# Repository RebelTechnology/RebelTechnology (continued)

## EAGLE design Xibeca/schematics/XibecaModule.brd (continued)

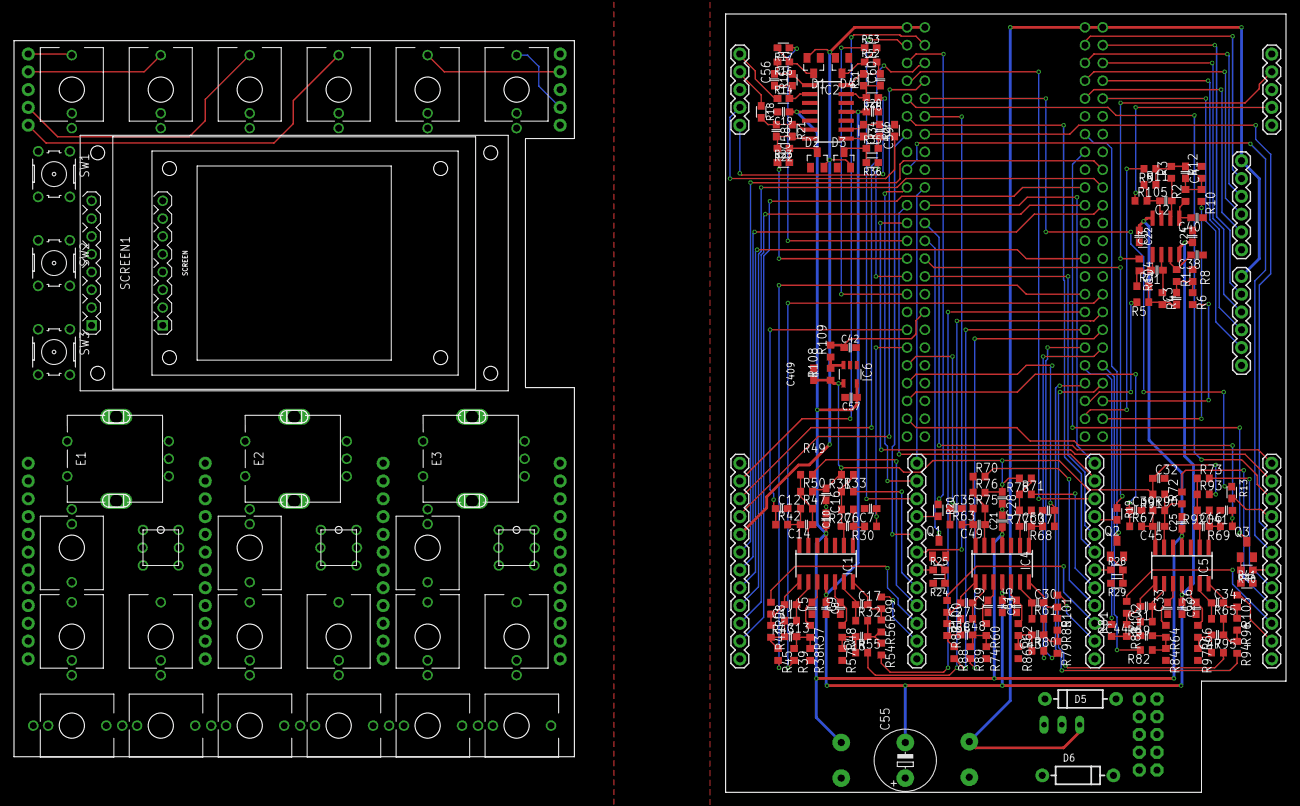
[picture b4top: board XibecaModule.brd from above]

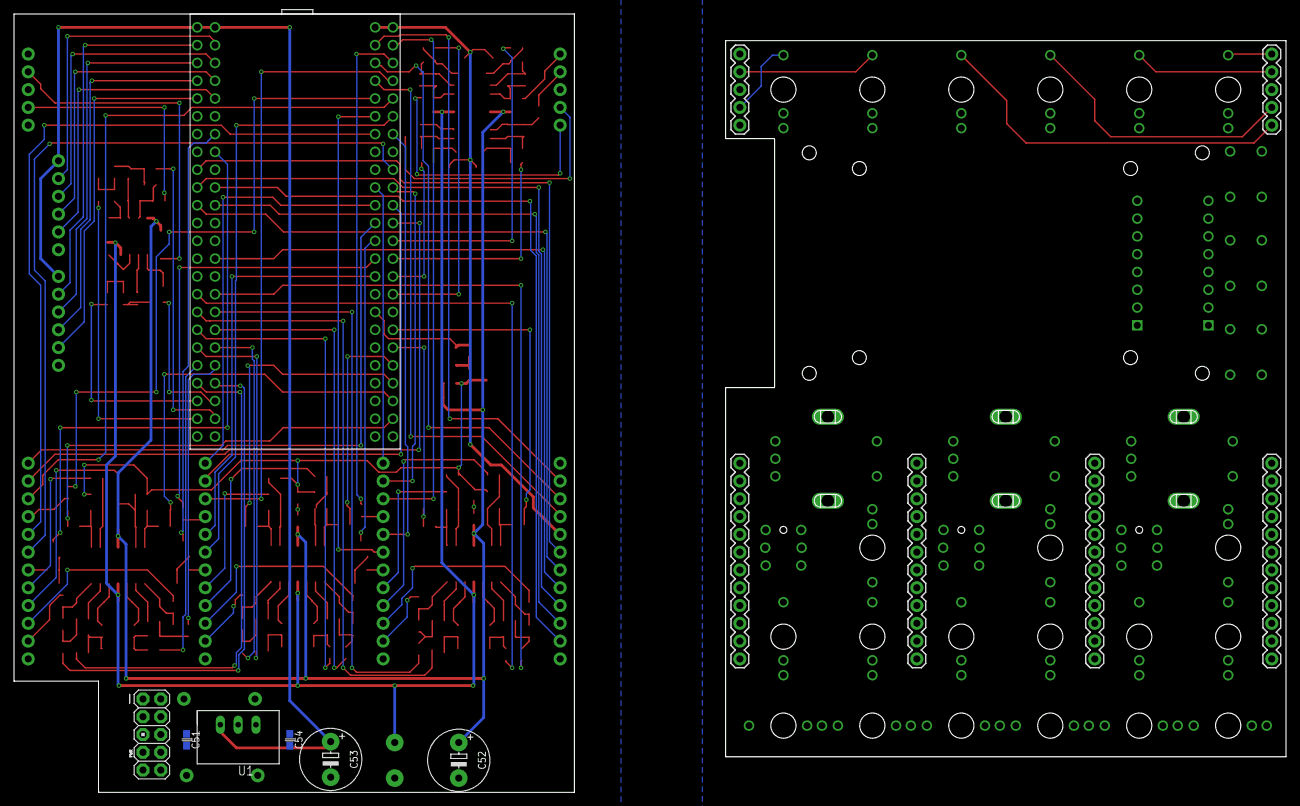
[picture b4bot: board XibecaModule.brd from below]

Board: 2 copper layers, 80.0 x 111.1 mm, 232 parts (13 on the bottom side), 183 nets.

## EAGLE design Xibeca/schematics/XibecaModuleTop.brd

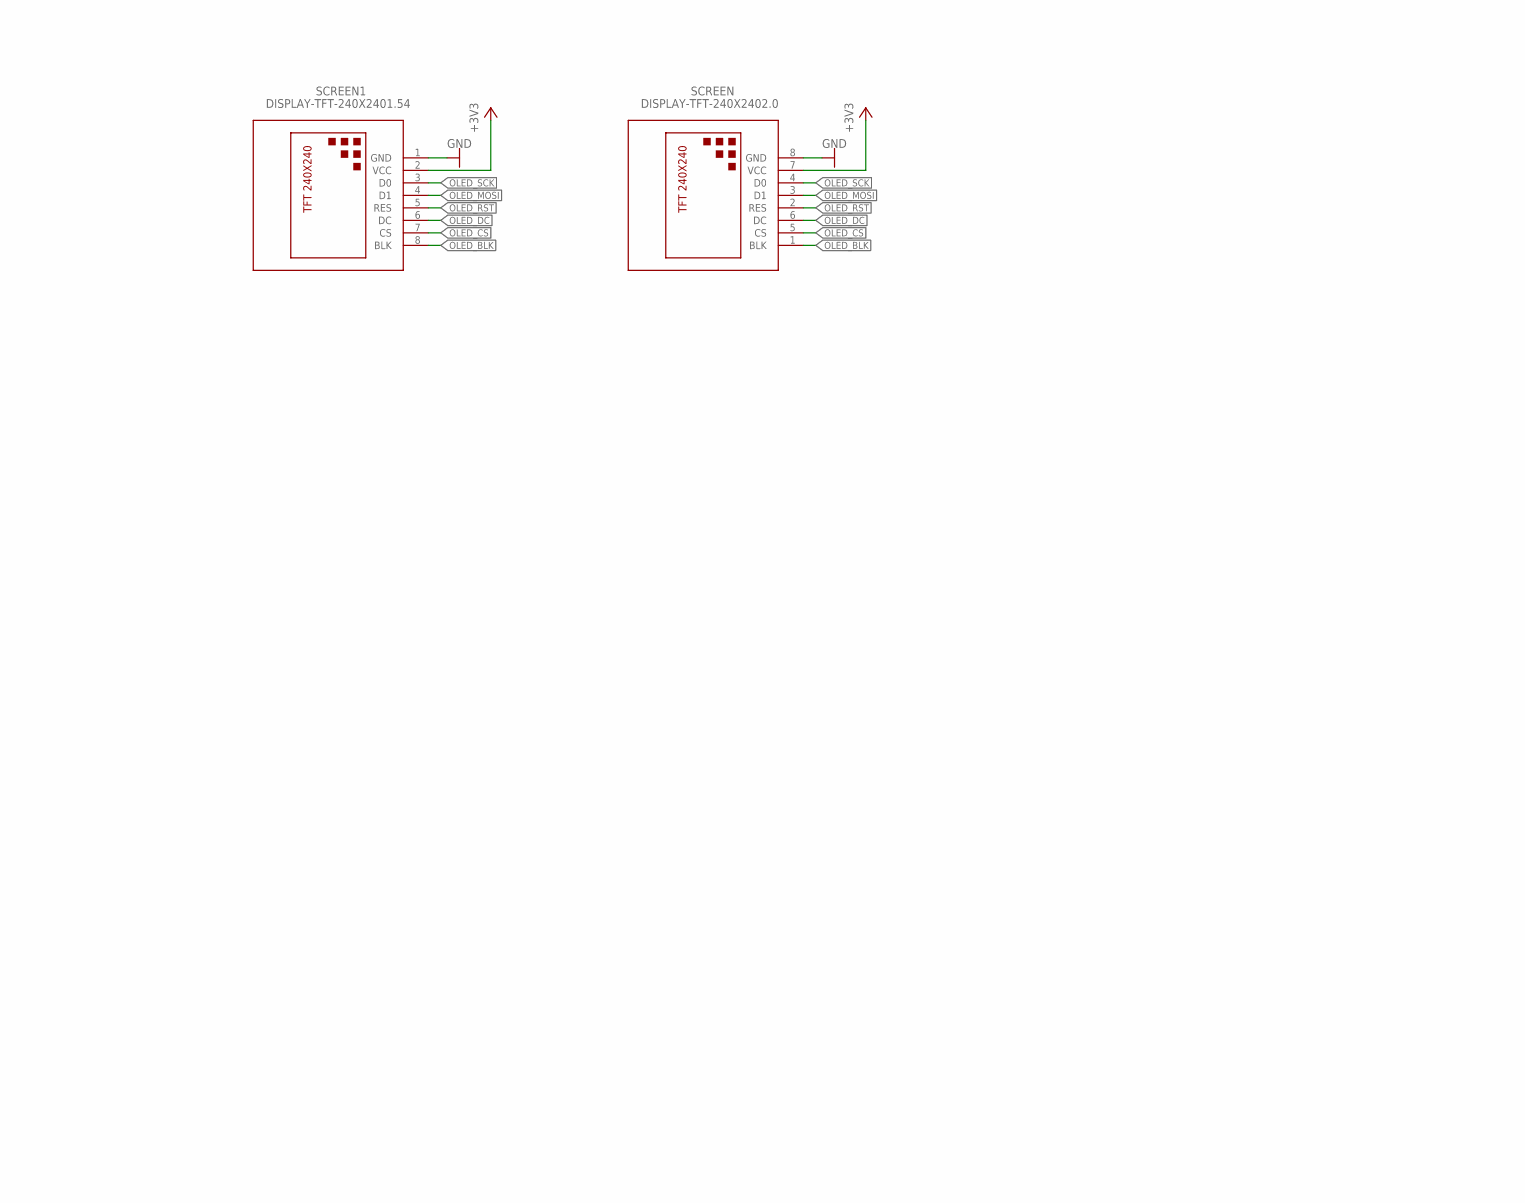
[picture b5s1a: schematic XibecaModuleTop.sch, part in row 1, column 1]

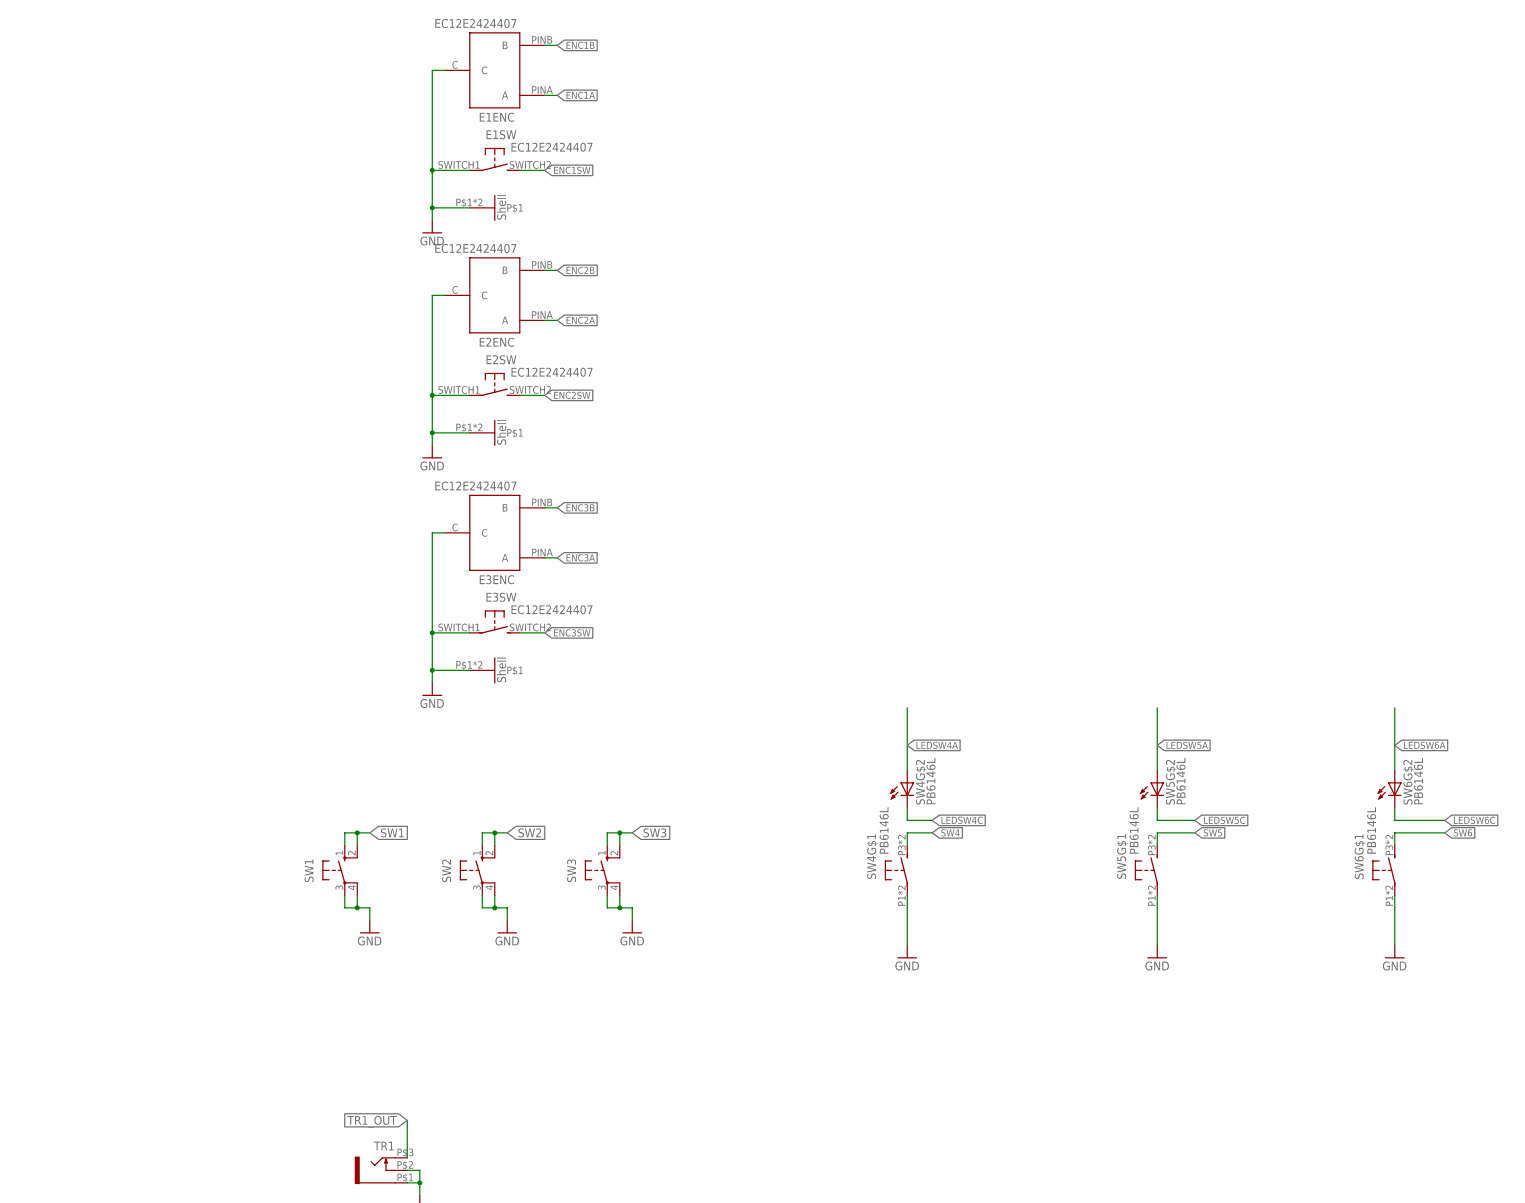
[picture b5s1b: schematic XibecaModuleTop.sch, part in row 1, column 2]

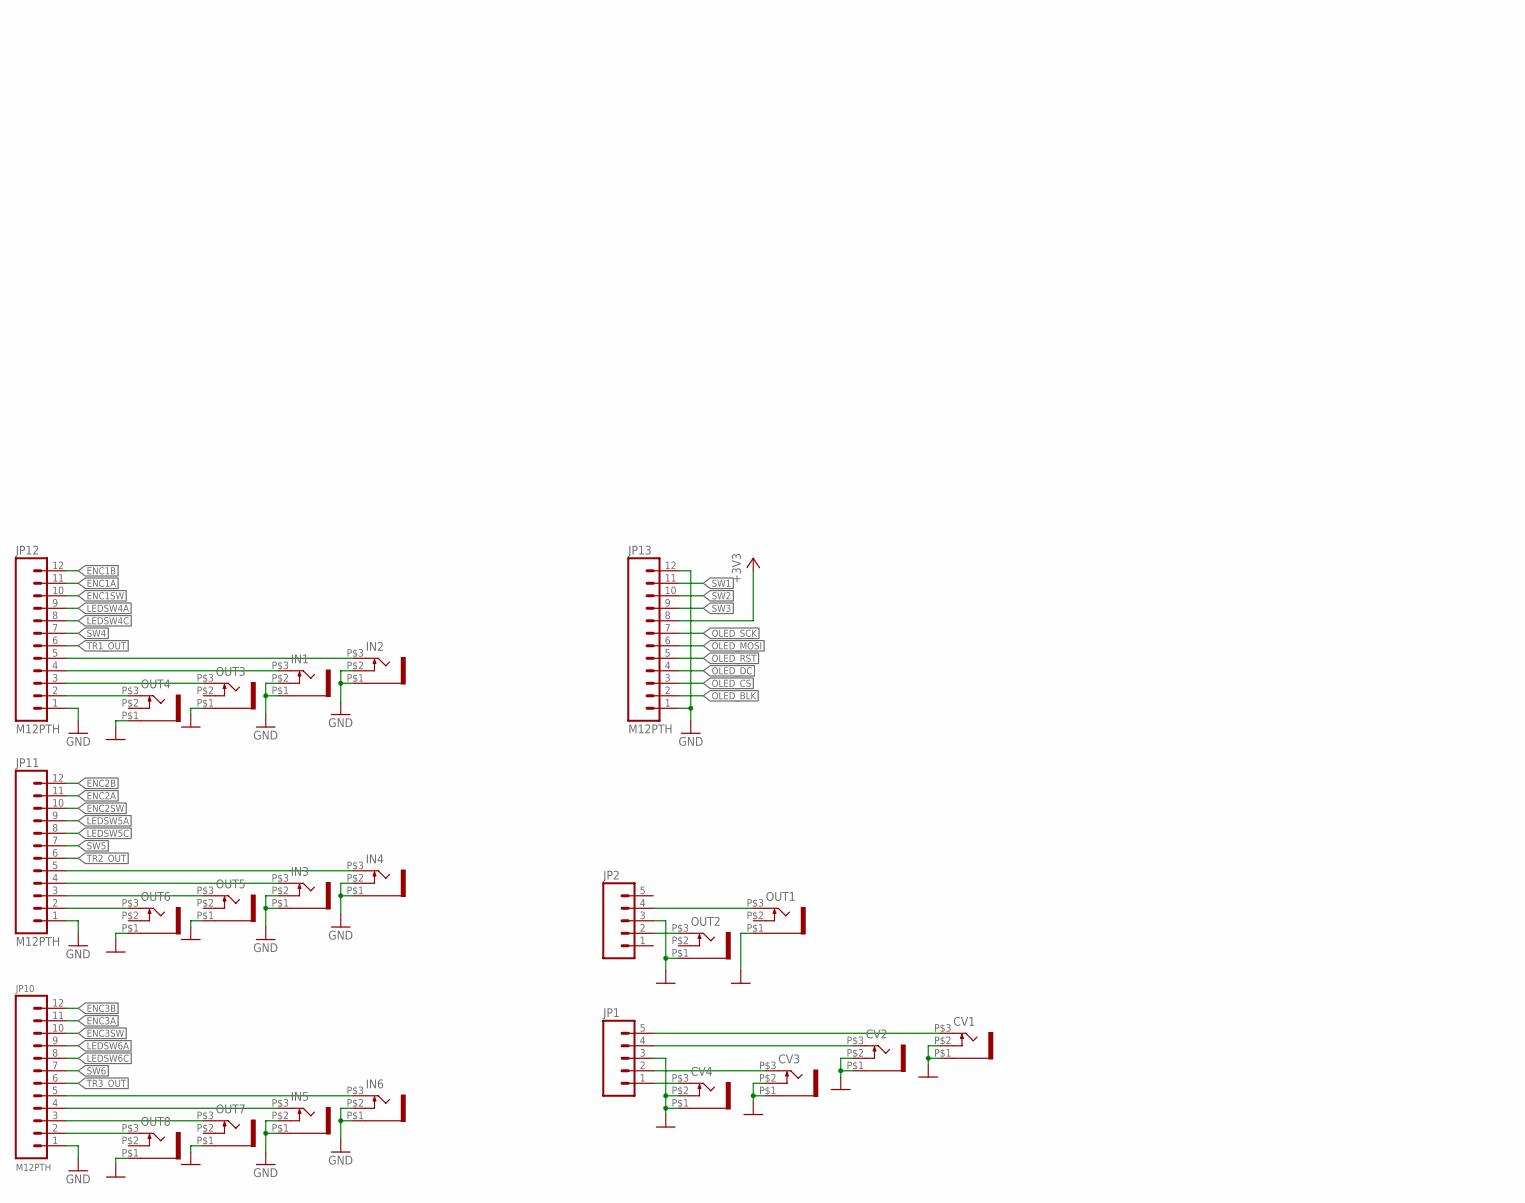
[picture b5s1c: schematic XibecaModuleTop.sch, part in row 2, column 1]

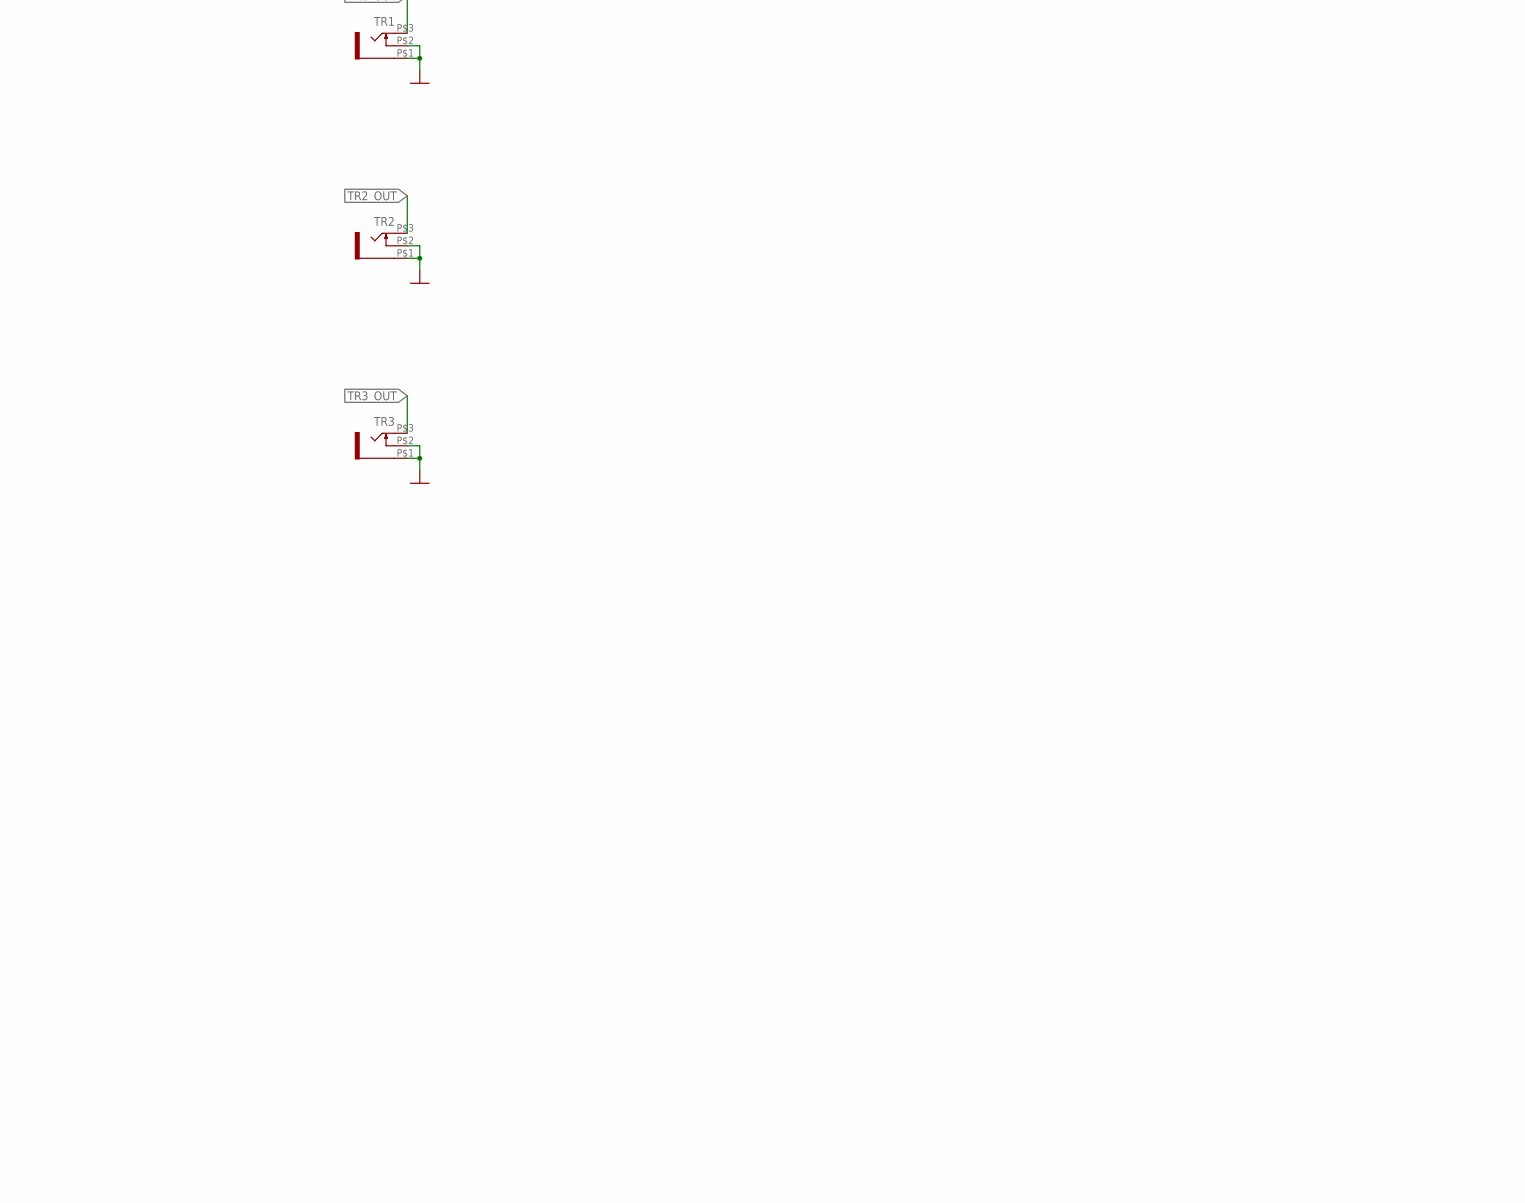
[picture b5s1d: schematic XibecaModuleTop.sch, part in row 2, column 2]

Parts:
CV1, CV2, CV3, CV4: THONKICONN
E1, E2, E3: EC12E2424407
IN1, IN2, IN3, IN4, IN5, IN6: THONKICONN
JP1, JP2: M05PTH; 1X05
JP10, JP11, JP12, JP13: M12PTH; 1X12
OUT1, OUT2, OUT3, OUT4, OUT5, OUT6, OUT7, OUT8: THONKICONN
SCREEN: DISPLAY-TFT-240X2402.0; DISPLAY-TFT-240X320-2.0"
SCREEN1: DISPLAY-TFT-240X2401.54; DISPLAY-TFT-240X240-1.54"
SW1, SW2, SW3: 10-XX; B3F-10XX
SW4, SW5, SW6: PB6146L
TR1, TR2, TR3: THONKICONN

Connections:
+3V3: JP13.8, SCREEN.7 (VCC), SCREEN1.2 (VCC)
ENC1A: E1.PINA (A), JP12.11
ENC1B: E1.PINB (B), JP12.12
ENC1SW: E1.SWITCH2 (S), JP12.10
ENC2A: E2.PINA (A), JP11.11
ENC2B: E2.PINB (B), JP11.12
ENC2SW: E2.SWITCH2 (S), JP11.10
ENC3A: E3.PINA (A), JP10.11
ENC3B: E3.PINB (B), JP10.12
ENC3SW: E3.SWITCH2 (S), JP10.10
GND: CV1.P$1 (5), CV1.P$2 (4), CV2.P$1 (5), CV2.P$2 (4), CV3.P$1 (5), CV3.P$2 (4), CV4.P$1 (5), CV4.P$2 (4), E1.C, E1.P$1, E1.P$2, E1.SWITCH1, E2.C, E2.P$1, E2.P$2, E2.SWITCH1, E3.C, E3.P$1, E3.P$2, E3.SWITCH1, IN1.P$1 (5), IN1.P$2 (4), IN2.P$1 (5), IN2.P$2 (4), IN3.P$1 (5), IN3.P$2 (4), IN4.P$1 (5), IN4.P$2 (4), IN5.P$1 (5), IN5.P$2 (4), IN6.P$1 (5), IN6.P$2 (4), JP1.3, JP2.3, JP10.1, JP11.1, JP12.1, JP13.1, JP13.12, OUT1.P$1 (5), OUT2.P$1 (5), OUT3.P$1 (5), OUT4.P$1 (5), OUT5.P$1 (5), OUT6.P$1 (5), OUT7.P$1 (5), OUT8.P$1 (5), SCREEN.8 (GND), SCREEN1.1 (GND), SW1.3, SW1.4 (P1), SW2.3, SW2.4 (P1), SW3.3, SW3.4 (P1), SW4.P1, SW4.P2, SW5.P1, SW5.P2, SW6.P1, SW6.P2, TR1.P$1 (5), TR1.P$2 (4), TR2.P$1 (5), TR2.P$2 (4), TR3.P$1 (5), TR3.P$2 (4)
LEDSW4A: JP12.9, SW4.PL1 (A)
LEDSW4C: JP12.8, SW4.PL2 (C)
LEDSW5A: JP11.9, SW5.PL1 (A)
LEDSW5C: JP11.8, SW5.PL2 (C)
LEDSW6A: JP10.9, SW6.PL1 (A)
LEDSW6C: JP10.8, SW6.PL2 (C)
unnamed: IN2.P$3 (3), JP12.5
unnamed: IN1.P$3 (3), JP12.4
unnamed: JP12.3, OUT3.P$3 (3)
unnamed: JP12.2, OUT4.P$3 (3)
unnamed: JP11.2, OUT6.P$3 (3)
unnamed: JP11.3, OUT5.P$3 (3)
unnamed: JP2.4, OUT1.P$3 (3)
unnamed: JP2.2, OUT2.P$3 (3)
unnamed: IN3.P$3 (3), JP11.4
unnamed: IN4.P$3 (3), JP11.5
unnamed: JP10.2, OUT8.P$3 (3)
unnamed: JP10.3, OUT7.P$3 (3)
unnamed: IN5.P$3 (3), JP10.4
unnamed: IN6.P$3 (3), JP10.5
unnamed: CV4.P$3 (3), JP1.1
unnamed: CV1.P$3 (3), JP1.5
unnamed: CV2.P$3 (3), JP1.4
unnamed: CV3.P$3 (3), JP1.2
OLED_BLK: JP13.2, SCREEN.1 (BLK), SCREEN1.8 (BLK)
OLED_CS: JP13.3, SCREEN.5 (CS), SCREEN1.7 (CS)
OLED_DC: JP13.4, SCREEN.6 (DC), SCREEN1.6 (DC)
OLED_MOSI: JP13.6, SCREEN.3 (D1), SCREEN1.4 (D1)
OLED_RST: JP13.5, SCREEN.2 (RES), SCREEN1.5 (RES)
OLED_SCK: JP13.7, SCREEN.4 (D0), SCREEN1.3 (D0)
SW1: JP13.11, SW1.1 (S), SW1.2 (S1)
SW2: JP13.10, SW2.1 (S), SW2.2 (S1)
SW3: JP13.9, SW3.1 (S), SW3.2 (S1)
SW4: JP12.7, SW4.P3 (S), SW4.P4 (S)
SW5: JP11.7, SW5.P3 (S), SW5.P4 (S)
SW6: JP10.7, SW6.P3 (S), SW6.P4 (S)
TR1_OUT: JP12.6, TR1.P$3 (3)
TR2_OUT: JP11.6, TR2.P$3 (3)
TR3_OUT: JP10.6, TR3.P$3 (3)

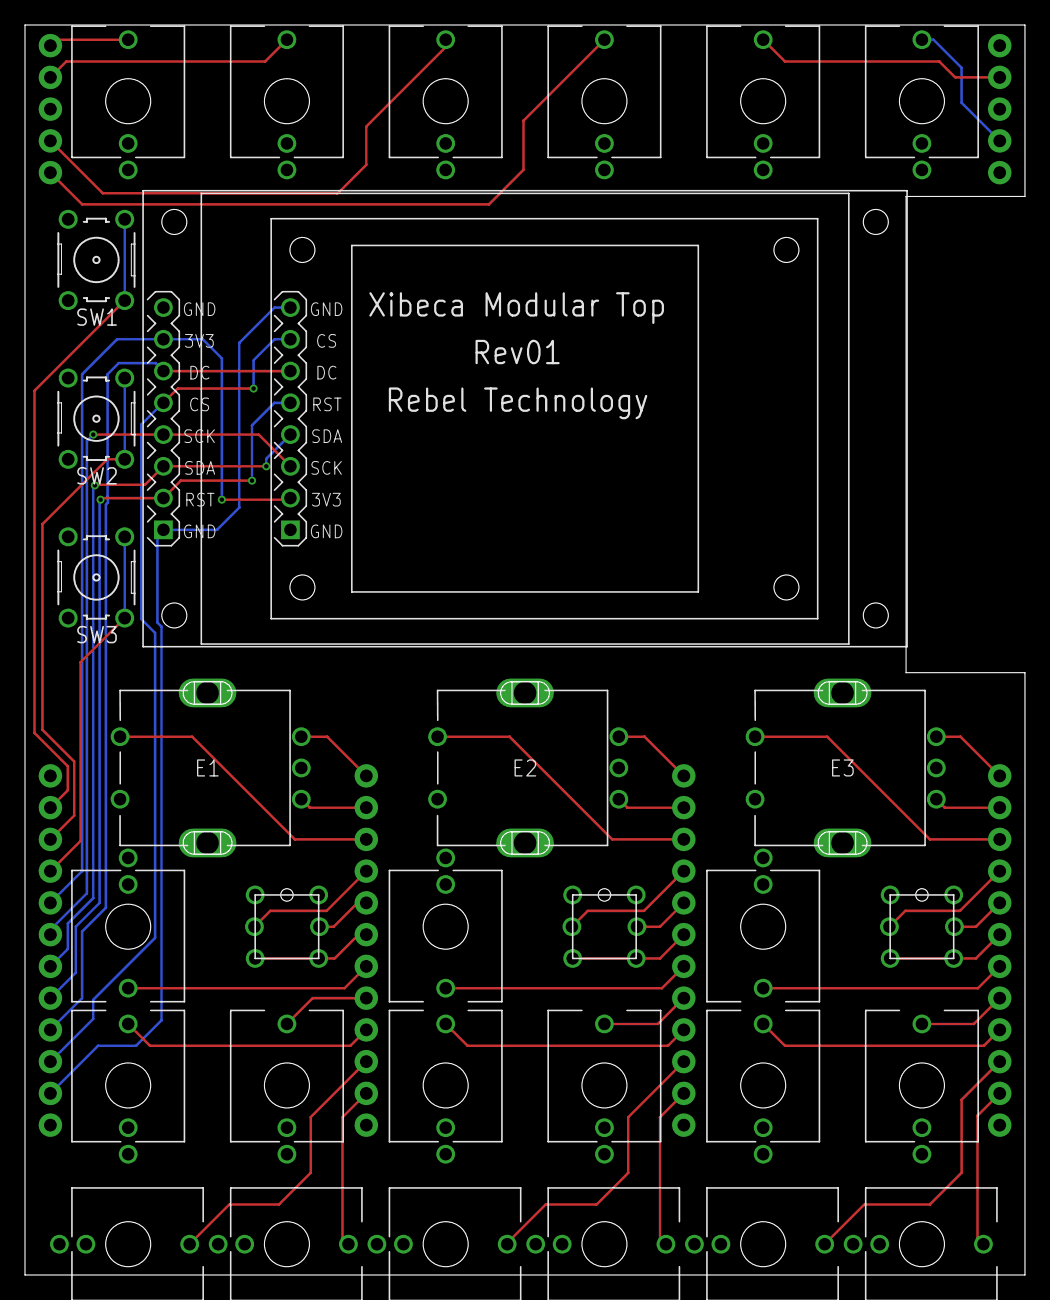
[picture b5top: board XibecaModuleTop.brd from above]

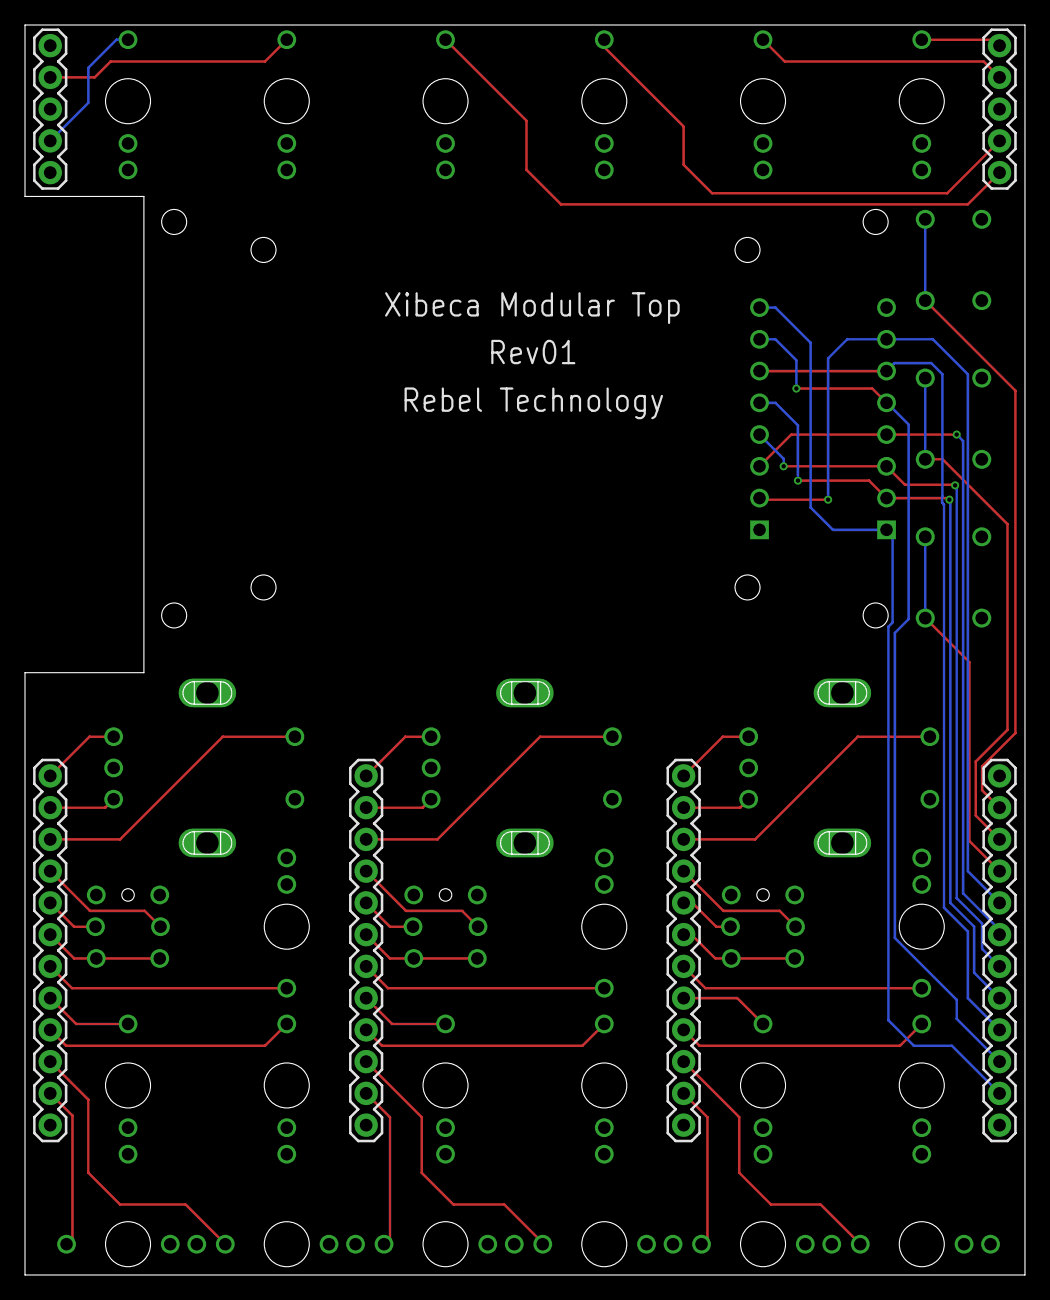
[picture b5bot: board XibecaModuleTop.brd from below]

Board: 2 copper layers, 80.0 x 100.0 mm, 38 parts (6 on the bottom side), 50 nets.

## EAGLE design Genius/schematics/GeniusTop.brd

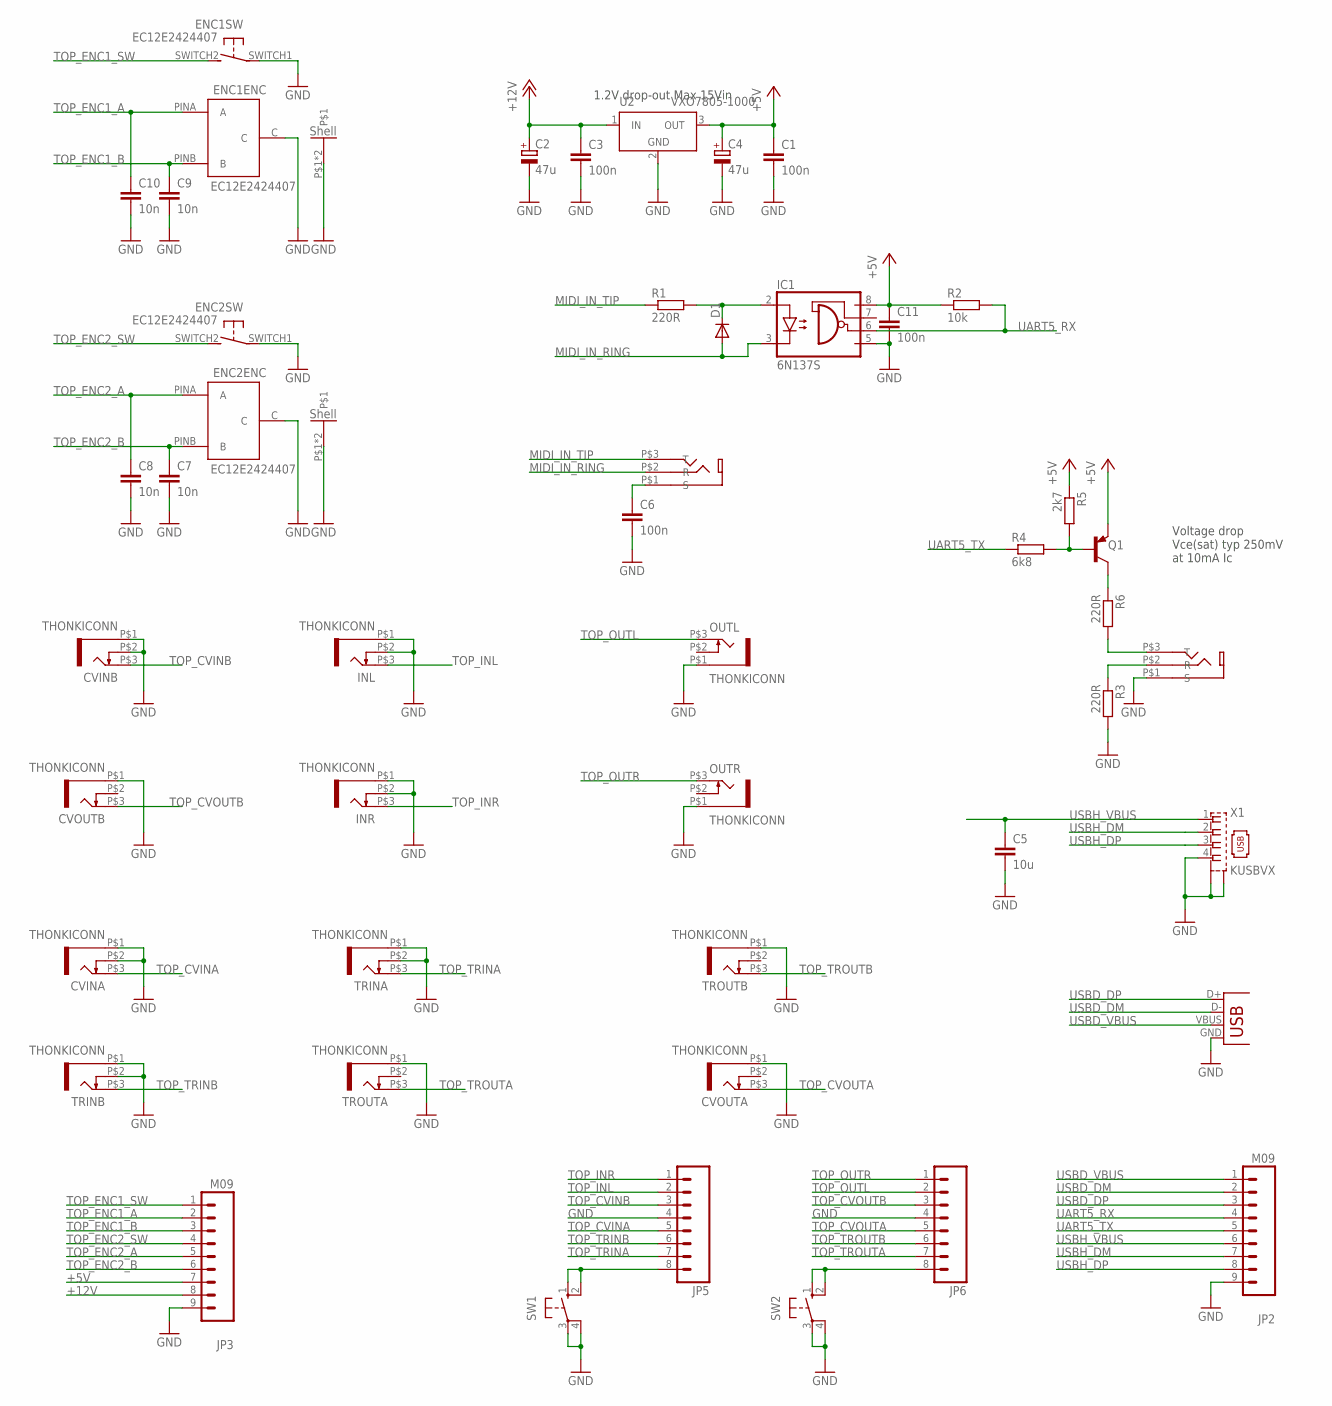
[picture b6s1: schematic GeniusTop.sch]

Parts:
C1, C3, C6, C11: 100n; C0603
C2, C4: 47u; CPOL-5
C5: 10u; C1206
C7, C8, C9, C10: 10n; C0603
CVINA: THONKICONN
CVINB: THONKICONN
CVOUTA: THONKICONN
CVOUTB: THONKICONN
D1: DIODESOD-123; SOD-123
ENC1, ENC2: EC12E2424407
IC1: 6N137S; DIL8-SMD
INL: THONKICONN
INR: THONKICONN
JP2, JP3: M09; 1X09
JP5, JP6: M081X08; 1X08
MIDI_IN: THONKICONN_STEREO
MIDI_OUT: THONKICONN_STEREO
OUTL: THONKICONN
OUTR: THONKICONN
Q1: MMBT3906LT1-PNP-SOT23-BEC; SOT23-BEC
R1, R3, R6: 220R; 0603
R2: 10k; 0603
R4: 6k8; 0603
R5: 2k7; 0603
SW1, SW2: 10-XX; B3F-10XX
TRINA: THONKICONN
TRINB: THONKICONN
TROUTA: THONKICONN
TROUTB: THONKICONN
U2: VXO7805-1000; TSR-1-2450
X1: KUSBVX
X2: USBPTH-VERTICAL; USB-B-PTH-VERTICAL

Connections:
+5V: C1.1, C4.+, C11.1, IC1.8 (VCC), JP3.7, Q1.E, R2.1, R5.1, U2.3 (OUT)
+12V: C2.+, C3.1, JP3.8, U2.1 (IN)
GND: C1.2, C2.-, C3.2, C4.-, C5.2, C6.2, C7.2, C8.2, C9.2, C10.2, C11.2, CVINA.P$1 (5), CVINA.P$2 (4), CVINB.P$1 (5), CVINB.P$2 (4), CVOUTA.P$1 (5), CVOUTB.P$1 (5), ENC1.C, ENC1.P$1, ENC1.P$2, ENC1.SWITCH1, ENC2.C, ENC2.P$1, ENC2.P$2, ENC2.SWITCH1, IC1.5 (GND), INL.P$1 (5), INL.P$2 (4), INR.P$1 (5), INR.P$2 (4), JP2.9, JP3.9, JP5.4, JP6.4, MIDI_OUT.P$1 (S), OUTL.P$1 (5), OUTR.P$1 (5), R3.2, SW1.3, SW1.4 (P1), SW2.3, SW2.4 (P1), TRINA.P$1 (5), TRINA.P$2 (4), TRINB.P$1 (5), TRINB.P$2 (4), TROUTA.P$1 (5), TROUTB.P$1 (5), U2.2 (GND), X1.4, X1.M1 (S1), X1.M2 (S2), X2.GND
MIDI_IN_RING: D1.A, IC1.3 (C), MIDI_IN.P$2 (R)
MIDI_IN_TIP: MIDI_IN.P$3 (T), R1.1
MIDI_OUT_TIP: MIDI_OUT.P$3 (T), R6.2
unnamed: D1.C, IC1.2 (A), R1.2
unnamed: C6.1, MIDI_IN.P$1 (S)
unnamed: JP5.8, SW1.1 (S), SW1.2 (S1)
unnamed: JP6.8, SW2.1 (S), SW2.2 (S1)
unnamed: Q1.B, R4.2, R5.2
unnamed: MIDI_OUT.P$2 (R), R3.1
unnamed: Q1.C, R6.1
TOP_CVINA: CVINA.P$3 (3), JP5.5
TOP_CVINB: CVINB.P$3 (3), JP5.3
TOP_CVOUTA: CVOUTA.P$3 (3), JP6.5
TOP_CVOUTB: CVOUTB.P$3 (3), JP6.3
TOP_ENC1_A: C10.1, ENC1.PINA (A), JP3.2
TOP_ENC1_B: C9.1, ENC1.PINB (B), JP3.3
TOP_ENC1_SW: ENC1.SWITCH2 (S), JP3.1
TOP_ENC2_A: C8.1, ENC2.PINA (A), JP3.5
TOP_ENC2_B: C7.1, ENC2.PINB (B), JP3.6
TOP_ENC2_SW: ENC2.SWITCH2 (S), JP3.4
TOP_INL: INL.P$3 (3), JP5.2
TOP_INR: INR.P$3 (3), JP5.1
TOP_OUTL: JP6.2, OUTL.P$3 (3)
TOP_OUTR: JP6.1, OUTR.P$3 (3)
TOP_TRINA: JP5.7, TRINA.P$3 (3)
TOP_TRINB: JP5.6, TRINB.P$3 (3)
TOP_TROUTA: JP6.7, TROUTA.P$3 (3)
TOP_TROUTB: JP6.6, TROUTB.P$3 (3)
UART5_RX: IC1.6 (VO), JP2.4, R2.2
UART5_TX: JP2.5, R4.1
USBD_DM: JP2.2, X2.D-
USBD_DP: JP2.3, X2.D+
USBD_VBUS: JP2.1, X2.VBUS
USBH_DM: JP2.7, X1.2
USBH_DP: JP2.8, X1.3
USBH_VBUS: C5.1, JP2.6, X1.1

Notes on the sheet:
1.2V drop-out Max 15Vin
Voltage drop Vce(sat) typ 250mV at 10mA Ic

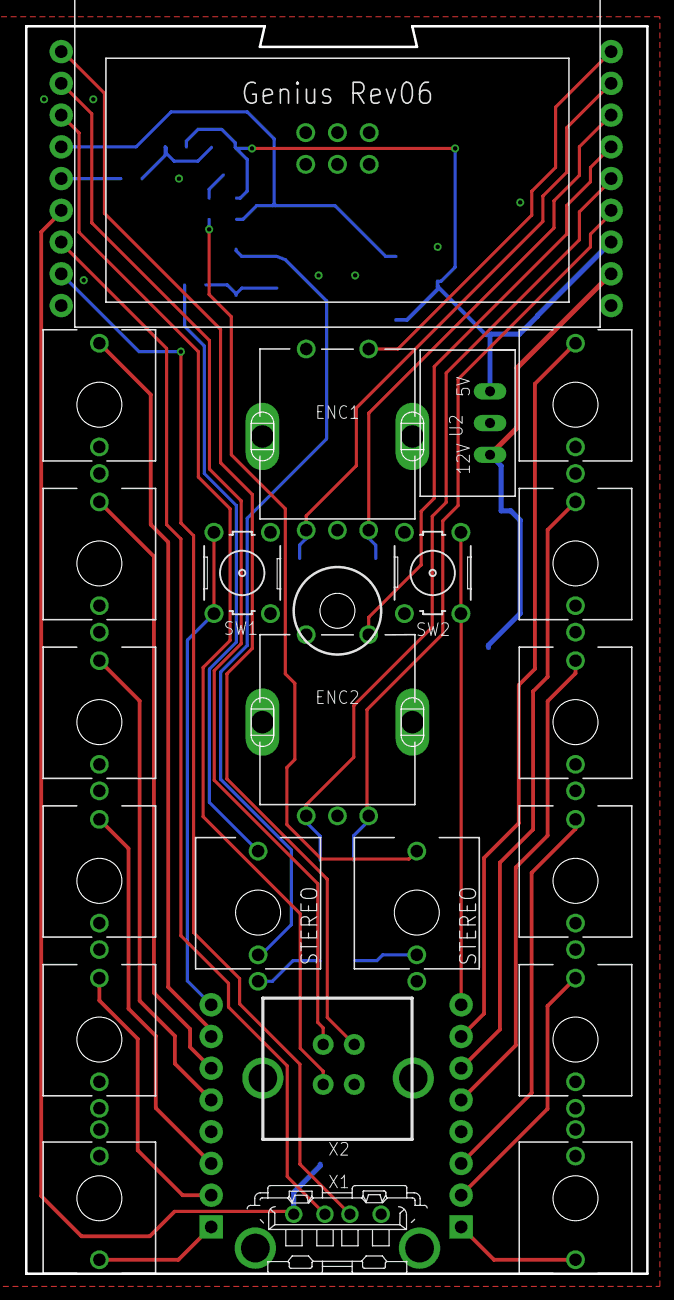
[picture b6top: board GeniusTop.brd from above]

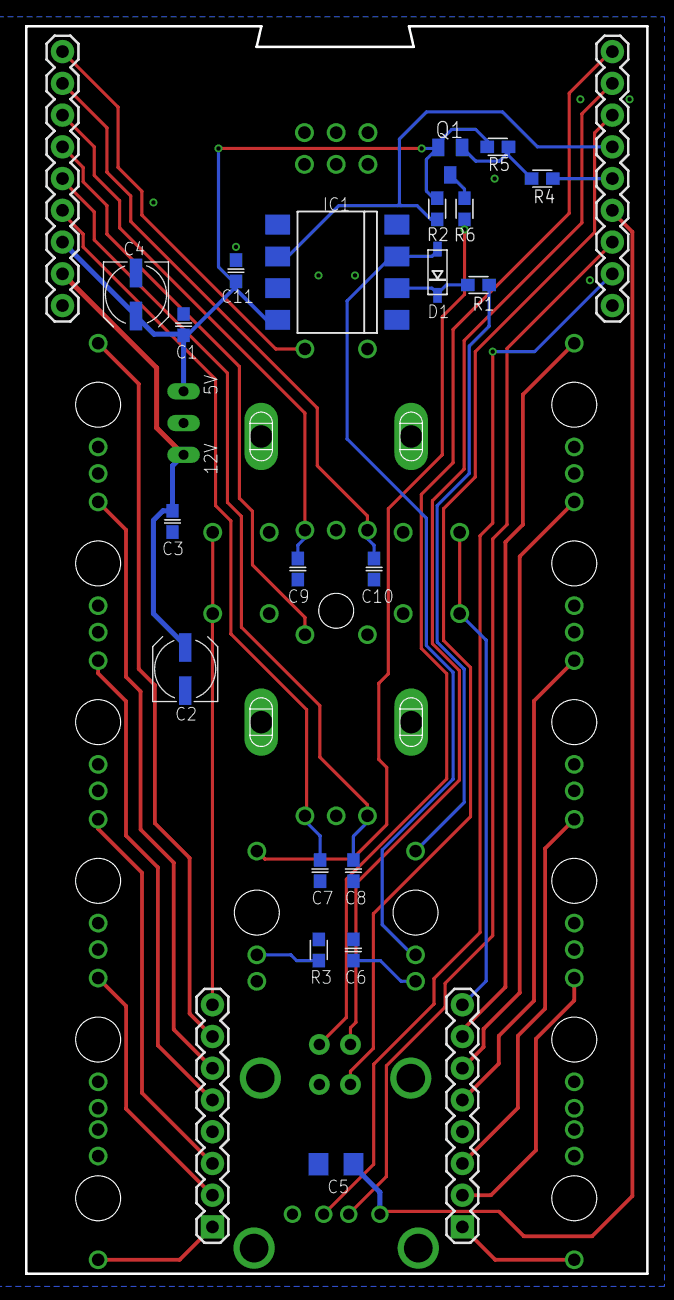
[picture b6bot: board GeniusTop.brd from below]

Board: 2 copper layers, 49.7 x 99.8 mm, 46 parts (24 on the bottom side), 39 nets.

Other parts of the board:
HLD1: SCREEN_HOLDER; OLED_128X64_1_54@1
